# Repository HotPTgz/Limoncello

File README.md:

# Limoncello 🍋🎻

**Limoncello is a successor to the [LMN-3](https://github.com/FundamentalFrequency), the open-source DIY groovebox by Fundamental Frequency.** The LMN-3 is a lemon tree; Limoncello is what you make from the lemons, and it ends in *cello*.

It keeps the LMN-3's idea (a Raspberry Pi running a Tracktion-based DAW, a Teensy reading keys and encoders) and rebuilds the instrument around it:

| | Limoncello |
|---|---|
| Keys | 46 **Hall-effect** magnetic switches, **velocity-sensitive**, each with its own **RGB LED** |
| Screen | **7.9" 1280 × 400** bar screen (Waveshare), with DAW screens laid out for it |
| Audio | **Raspberry Pi Codec Zero** on board: two built-in **speakers**, a switched **headphone jack**, a **microphone** |
| Computer | **Raspberry Pi 5** with the official Active Cooler (the board is cut out around it) + **Teensy 4.1** |
| New controls | **MIC** key (record or sample from the mic), **joystick click** (sustain), Control + click (mod wheel on/off) |
| Case | 3D-printed, **flat top**: screen, speakers and keys flush; encoders in a sunken pocket; two lid options |
| Power | mains, or an optional **power bank cradle** (4.5–5 h) |

> **Project status: prototype.** The board, case, firmware and software are designed and checked in CAD and in simulation: design rule checks, interference checks between every part, unit tests, and the app running on a computer. A full Limoncello has **not been built yet**. A 4-key test board is being made to confirm the Hall-effect keys before the main board is ordered. See [What's still open](#whats-still-open).

## Where everything is

| Folder | What's in it |
|---|---|
| [`hardware/main-board/`](hardware/main-board) | The main PCB (rev C, 330 × 180 mm, 2 layers): KiCad project, Gerbers ready for JLCPCB/PCBWay, BOM, pick-and-place, 3D model, key map |
| [`hardware/test-board/`](hardware/test-board) | A 4-key test board and sketch, to try the Hall-effect keys before ordering the big board |
| [`enclosure/`](enclosure) | The printed case: OpenSCAD sources and ready-to-print STLs, the flush-key test piece, the power bank cradle, renders |
| [`firmware/`](firmware) | Teensy 4.1 firmware (PlatformIO): keys, velocity, LEDs, encoders, joystick |
| Software | The DAW lives in its own repository, because it is GPL: **[HotPTgz/lmn-3-daw, branch `lmn3-v3-wide`](https://github.com/HotPTgz/lmn-3-daw/tree/lmn3-v3-wide)** |
| [`docs/`](docs) | The [build guide](docs/BUILD.md), [shopping list](docs/SHOPPING_LIST.md), [software setup](docs/SOFTWARE.md), [controls](docs/CONTROLS.md), [power](docs/POWER.md) and [what has been verified](docs/VERIFICATION.md) |

## Build it

Start with **[docs/BUILD.md](docs/BUILD.md)**. It goes from ordering parts to the first sound, in this order:

1. Try the keys on the **test board** (optional, cheap, recommended).
2. Order the **parts** ([shopping list](docs/SHOPPING_LIST.md)) and the **main board**.
3. **Assemble** the board, flash the **Teensy**.
4. Set up the **Raspberry Pi** and build the **software** ([SOFTWARE.md](docs/SOFTWARE.md)).
5. **Print** and assemble the **case**.

Roughly: $520 of core parts, plus either $200 for factory assembly of the small surface-mount parts or $35 of parts to solder yourself. The battery option is about $90 more.

## A look inside

| | |
|---|---|
|  |  |
| The DAW's screens laid out for the 7.9" bar: the knob boxes sit in a 2 × 2 grid, like the encoders beside the screen | Control + MIC samples a sound straight onto a drum pad or into the sampler |
|  |  |
| The Pi 5 hangs under the board; the board is cut around its cooler, measured from Raspberry Pi's official 3D model | The optional power bank cradle also tilts the instrument 8° towards you |

## What's still open

- **The screen's HDMI cable route.** The Pi's micro-HDMI ports sit at the rear wall, while the screen's HDMI port is inside, so the cable either loops outside the case or goes through a micro-HDMI ribbon kit. Neither is built into the case yet. See [BUILD.md](docs/BUILD.md#the-screens-hdmi-cable).
- **The key gap** (`GAP` in the case) will be set from the flush-key test piece.
- **The joystick height** used for the lids is an estimate. Measure it when you have one.
- **Recording from the mic onto a track** and the app on the real 7.9" screen still need trying on real hardware.

Issues and pull requests are welcome, especially from people who build one.

## Credits and licences

Limoncello stands on the **LMN-3 by [Fundamental Frequency](https://github.com/FundamentalFrequency)**: [LMN-3-ECAD](https://github.com/FundamentalFrequency/LMN-3-ECAD), [LMN-3-DAW](https://github.com/FundamentalFrequency/LMN-3-DAW) and [LMN-3-Firmware](https://github.com/FundamentalFrequency/LMN-3-Firmware). The DAW is built on [Tracktion Engine](https://github.com/Tracktion/tracktion_engine) and [JUCE](https://juce.com).

| Part | Licence |
|---|---|
| Hardware (`hardware/`) and enclosure (`enclosure/`) | [CC BY-SA 4.0](LICENSES/CC-BY-SA-4.0.txt), like the LMN-3 hardware it derives from |
| Firmware (`firmware/`) | [GPL-3.0](firmware/LICENSE), like LMN-3-Firmware |
| Software ([lmn-3-daw fork](https://github.com/HotPTgz/lmn-3-daw)) | GPL-3.0, like LMN-3-DAW |
| `enclosure/source/pi5_official.stl` | Raspberry Pi Ltd's Pi 5 3D model, MIT ([licence](enclosure/source/pi5_official.LICENSE.txt)) |

Raspberry Pi is a trademark of Raspberry Pi Ltd. Waveshare, UGREEN, Gateron and the other product names belong to their owners; they are named only to say which parts fit.

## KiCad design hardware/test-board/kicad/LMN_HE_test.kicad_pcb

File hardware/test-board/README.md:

# Limoncello Hall-effect key test board

This is a 4-key test board that uses exactly the same key footprint as rev C:
- the MT9105ET Hall sensor under the switch;
- the SK6812MINI-E LED with its window and 100 nF capacitor;
- the same 74AHCT1G125 LED data buffer.

Use it to check that the sensor and Gateron magnetic switch combination works before you order the full 330 × 180 mm board.
The board is 87 × 42 mm, 2 layers. Design check (DRC): 0 errors, 0 unconnected.

## What's in here
| File | Use |
|---|---|
| `LMN_HE_test_gerbers.zip` | Upload to JLCPCB (2 layers, 1.6 mm, any colour). Five boards cost a few dollars. |
| `LMN_HE_test_BOM.csv`, `*_positions.csv` | Parts list and KiCad placement file. |
| `jlcpcb/` | Ready-to-upload files for having JLCPCB solder the SMD parts (BOM + CPL with LCSC numbers, Gerber zip). See its README. |
| `plate/test_plate.stl` (+ `.scad`) | 3D-printable switch plate: 1.5 mm plate on 3.5 mm legs, M2 screws. |
| `firmware/` | Test sketch for the Teensy 4.1 (PlatformIO or Arduino IDE). |
| `kicad/` | KiCad 7 project. |

## Parts to buy

If JLCPCB assembled your boards, skip the LCSC list: you only need the rest.

**From LCSC** (they sell passives in strips of 20–100, so you get spares for cents):

| Part | Refs | Qty to order | LCSC |
|---|---|---|---|
| MT9105ET Hall sensor, SOT-23 | SW1–SW4 | 10 (4 + spares) | C967861 |
| SK6812MINI-E reverse-mount LED | LED1–LED4 | 5 | C5149201 |
| 74AHCT1G125 buffer, SOT-23-5 | U1 | 5 (minimum order) | C12494 |
| 100 nF 0805 | C1–C5 | 1 strip | C49678 |
| 1 µF 0805 | C7 | 1 strip | C28323 |
| 330 Ω 0805 | R1 | 1 strip | C17630 |
| 10 µF 1206 (22 µF is fine too) | C6 | 1 strip | C12891 (22 µF) |

**Other parts:**
- **Teensy 4.1** with pins. Your existing LMN-3's Teensy works for the test.
- **4 × Gateron Magnetic Jade switches.** Use the same switch you plan to use for the full build.
- **1 × 1×8 pin header**, 2.54 mm, plus **8 female–female jumper wires** to the Teensy. If your Teensy has no headers, use female–male wires to a breadboard instead.
- **4 × M2 nuts**, plus either **4 × M2×10 screws** (plate only) or **4 × M2×35 screws** (plate + flush test panel). Get the M2×35 if you'll print the flush test, which you should.
- **Micro-USB cable** (data, not charge-only) from the Teensy to your computer.

## Parts to print

| File | Qty | Notes |
|---|---|---|
| `plate/test_plate.stl` | 1 | Switch plate: holds the 4 switches. PLA, 0.2 mm, flat side down. Same file as `enclosure/flush_test/test_switch_plate.stl`. |
| `enclosure/flush_test/flush_test_panel.stl` | 1 | Flush-key test panel: a piece of the case top with 4 openings at gaps of 0.35, 0.45, 0.55 and 0.65 mm. Print it top-down, like the real top shell. |
| `enclosure/flush_test/flush_test_tiles_all.stl` | 1 set | The 4 key tiles: 2 white, 1 raised black, 1 menu tile (REC). Print in the colours and settings you'll use for the real keys. |

Print the panel and tiles on the printer and filament you'll use for the case, because the gap you pick depends on both.

## Assembly
1. **Top side:** solder the 4 Hall sensors. Keep them flat and centred on their pads, because that sets the distance to the magnet.
2. **Bottom side:**
   - Solder the LEDs. They sit in the windows, facing up through the board. The small triangle on the silkscreen marks pin 1.
   - Solder the capacitors, U1 and R1.
3. Solder the 1×8 header on the top side.
4. Screw the printed plate on, clip the 4 switches into the plate, and push them down until they sit flat on the board. HE switches have no metal pins: the plate is what holds them.

## Wiring to the Teensy 4.1
| Test board J1 | Teensy |
|---|---|
| 3V3 | 3.3V |
| GND | GND |
| 5V | VIN (USB 5 V) |
| LED | pin 17 |
| K1, K2, K3, K4 | pins 14, 15, 16, 18 |

These are the same pins the rev C board uses.

## Running the test
1. Flash `firmware/` with PlatformIO (`pio run -t upload`). Or open `LMN_HE_test/LMN_HE_test.ino` in the Arduino IDE with Teensyduino and set **Tools > USB Type: Serial + MIDI**.
2. Plug in the USB cable and **keep your hands off the keys for 2 seconds** while it measures the resting values. The LEDs go blue, then green.
3. Open the Serial Plotter to see the four readings live. Each LED goes from blue to red as you press its key.
4. Press every key all the way down a few times, both slowly and fast.
5. Type `r` in the serial monitor to get the report. It says **PASS** or **CHECK** for each key.
6. Optional:
   - Type `v`, then play: it shows the time between the two thresholds and the velocity of every note.
   - Open any synth or DAW on your computer: the keys play C, D, E and F with velocity.

## What the numbers mean
| Result | Meaning | What to do |
|---|---|---|
| **swing ≥ 200 counts, noise ≤ 10 p-p, keys within ±30 %** | Good: the sensor sees enough change and velocity will work well. | Order rev C as it is. |
| swing between 100 and 200 | It works, but the velocity resolution is coarse. | Still usable. Try a stronger-magnet switch, or lower `VEL_SLOW_US` in the main firmware's `config.h`. |
| swing < 100 | The sensor is too insensitive for this magnet, or a sensor sits crooked. | Re-check the soldering. If all keys are low, the sensor choice needs to change before ordering rev C. |
| noisy (> 10 p-p) | Supply or wiring noise. | Use short wires and twist GND with the signals. rev C has better grounding; the firmware can also average. |
| one key very different | Bad solder joint, tilted sensor, or a switch not seated flat. | Reflow that sensor or reseat the switch, then press `c` and test again. |

Keep the report (`r`) and a screenshot of the plotter: they tell you how to set the thresholds in `firmware/src/config.h` for your switches. If your results are unusual, please share them in an issue.

## Note for the full build
These switches need a **plate** (1.5 mm) to hold them. The rev C plate is printed in two halves: `enclosure/stl/plate_left.stl` and `plate_right.stl`.

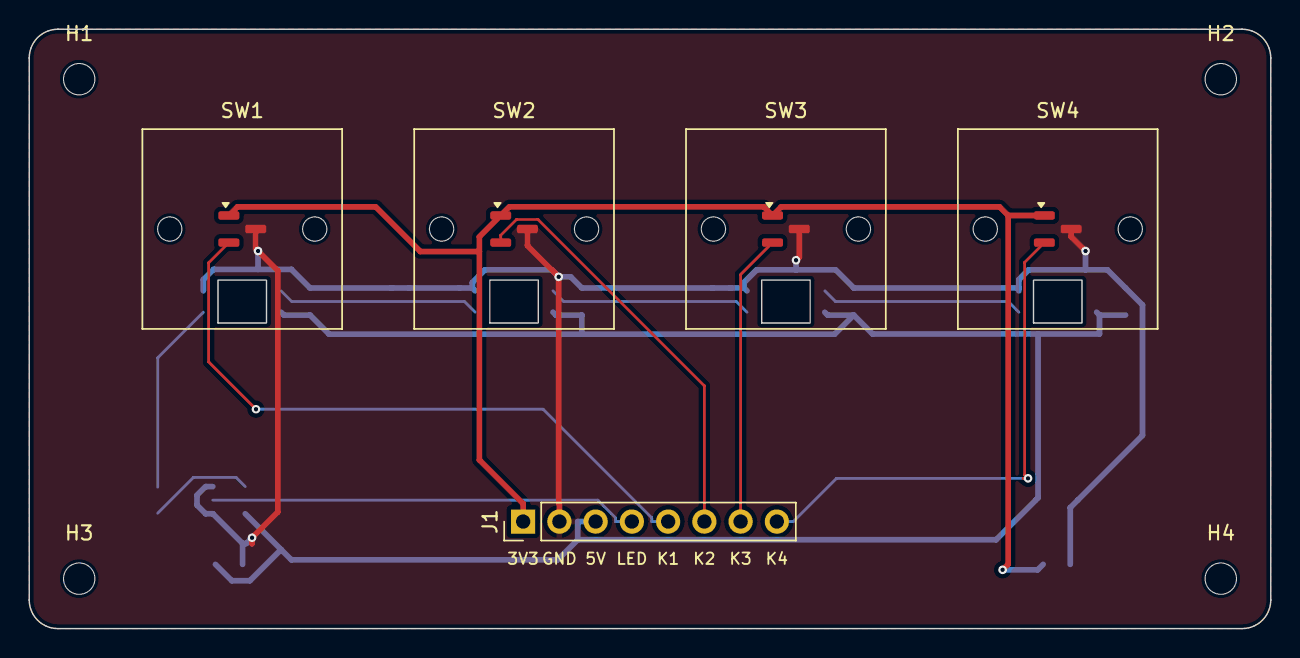
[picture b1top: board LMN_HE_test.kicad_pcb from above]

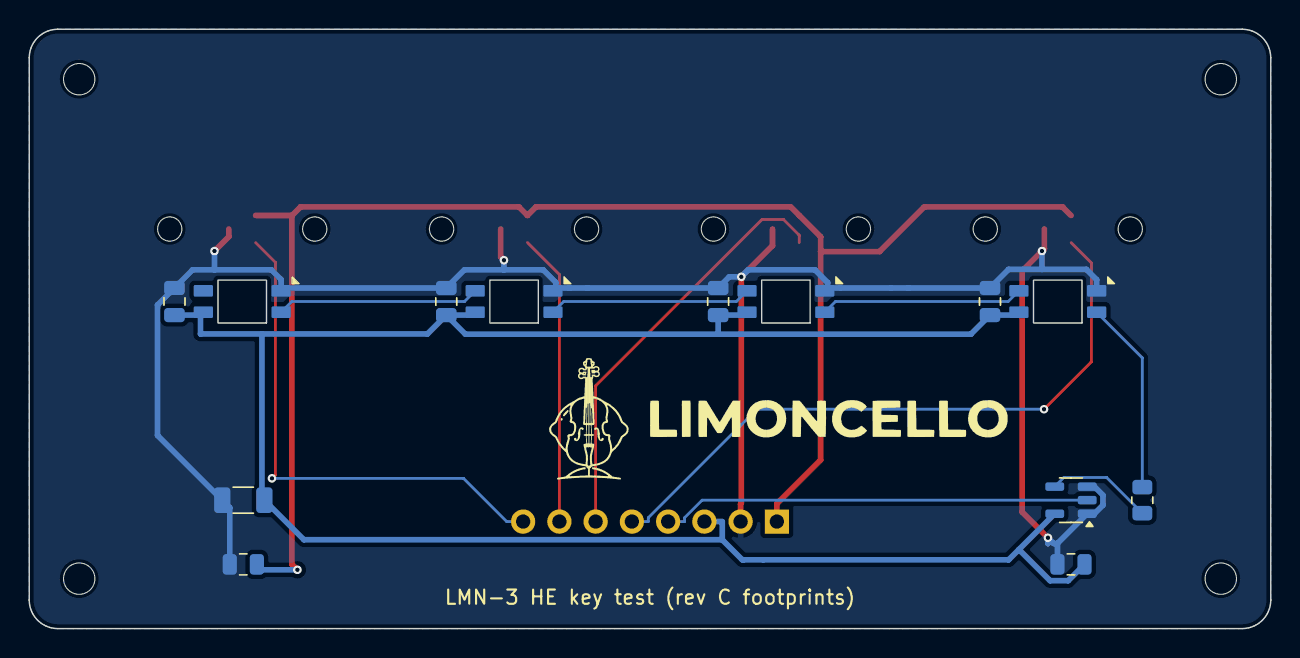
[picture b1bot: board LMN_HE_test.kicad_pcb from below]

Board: 2 copper layers, 87.0 x 42.0 mm, 23 parts (14 on the bottom side), 13 nets.

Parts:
C1, C2, C3, C4, C5: 100nF; C_0805_2012Metric
C6: 10uF; C_1206_3216Metric
C7: 1uF; C_0805_2012Metric
H1, H2, H3, H4: M2; MountingHole_2.2mm_M2
J1: To Teensy; PinHeader_1x08_P2.54mm_Vertical
LED1, LED2, LED3, LED4: SK6812MINI-E; SK6812MINI-E_MX_Reverse
LOGO1: Limoncello_badge_8mm
R1: 330R; R_0805_2012Metric
SW1, SW2, SW3, SW4: MT9105ET; SW_MX_HE_SOT23
U1: 74AHCT1G125; SOT-23-5

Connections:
+3V3: C7.1, J1.1, SW1.1, SW2.1, SW3.1, SW4.1
+5V: C1.1, C2.1, C3.1, C4.1, C5.1, C6.1, J1.3, LED1.1, LED2.1, LED3.1, LED4.1, U1.5
GND: C1.2, C2.2, C3.2, C4.2, C5.2, C6.2, C7.2, J1.2, LED1.3, LED2.3, LED3.3, LED4.3, SW1.3, SW2.3, SW3.3, SW4.3, U1.1, U1.3
LED_D0: LED1.4, R1.2
LED_D1: LED1.2, LED2.4
LED_D2: LED2.2, LED3.4
LED_D3: LED3.2, LED4.4
LED_DATA_3V3: J1.4, U1.2
LED_DATA_5V: R1.1, U1.4
OUT1: J1.5, SW1.2
OUT2: J1.6, SW2.2
OUT3: J1.7, SW3.2
OUT4: J1.8, SW4.2

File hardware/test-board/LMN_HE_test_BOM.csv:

Qty,Value,Footprint,Side,References
5,100nF,C_0805_2012Metric,bottom,C1 C2 C3 C4 C5
1,10uF,C_1206_3216Metric,bottom,C6
1,1uF,C_0805_2012Metric,bottom,C7
4,M2,MountingHole_2.2mm_M2,top,H1 H2 H3 H4
1,To Teensy,PinHeader_1x08_P2.54mm_Vertical,top,J1
4,SK6812MINI-E,SK6812MINI-E_MX_Reverse,bottom,LED1 LED2 LED3 LED4
1,330R,R_0805_2012Metric,bottom,R1
4,MT9105ET,SW_MX_HE_SOT23,top,SW1 SW2 SW3 SW4
1,74AHCT1G125,SOT-23-5,bottom,U1

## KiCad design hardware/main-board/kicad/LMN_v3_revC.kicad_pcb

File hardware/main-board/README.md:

# Limoncello main board (rev C): Hall-effect keys, RGB, 7.9" bar screen, Codec Zero audio

Board: 330 × 180 mm, 2 layers, 1.6 mm, GND pour on both layers.
DRC: 0 clearance errors, 0 unconnected. The only warnings left are silkscreen and library-path notices.

**Pi cooler opening (sized from the official Raspberry Pi drawings):** the rear edge is open over the Pi. Dimensions are measured from the board's left and rear edges.
- **Sources:** the Pi 5 STEP model and the Active Cooler mechanical drawing from Raspberry Pi.
- **Why it's needed:** the cooler stands about 10.5 mm above the Pi's top face. The gap between the Pi and this board (header plastic + socket) is 11 mm, so the cooler and its push pins need room above it.
- **Shape:** the opening runs x 107.5–197.3 mm, in three depth steps:
  - x 107.5–130.5: 56.5 mm deep, for the USB/Ethernet stack, which overhangs the Pi by 3 mm.
  - x 130.5–190.5: 50.3 mm deep, over the cooler body and fins.
  - x 190.5–197.3: 14.5 mm deep. The cooler corner here is empty, which leaves a routing corridor next to the GPIO header.
- **USB:** only the **lower** two USB ports and Ethernet are reachable. The board edge covers the upper USB pair.
- **Cables:** the opening also passes the HDMI and USB-C cables.
- **Mounting:** the cooler uses the Pi's two dedicated heatsink holes. The Pi is held by the GPIO header, **one M2.5 stand-off (H12)**, and three posts in the bottom tray under its other mounting holes. H11 was removed to make room for routing.
- **Routing:** the Pi → Codec Zero connections were re-routed around the opening.
  - Pin 17 (the second 3.3 V pin) is left unconnected on both J2 and J3. The Pi and the Codec Zero each tie it to pin 1 on their own board, so J2.1 → J3.1 feeds 3.3 V.
  - GPIO23/24/27 (the Codec Zero's LEDs and button) are no longer wired: they would be hidden inside the case anyway.

## What's on the board
- 46 Hall-effect keys (MT9105ET, per switch), 46 SK6812MINI-E LEDs, 6 × 74HC4051 → Teensy 4.1 (same as rev B, new layout).
- J2: underside socket for the Raspberry Pi 5 (held by the header, 1 M2.5 stand-off (H12) and 3 tray posts).
- **Audio**:
  - **J3:** a 2×20 male header wired in parallel with J2. The **Raspberry Pi Codec Zero** plugs onto it from below.
    - Its 40-pin female header goes onto J3, with its component side facing the case floor.
    - Its outline is drawn on Cmts.User/B.Fab.
  - **U9:** a PAM8403 stereo class-D amp, fed from the Codec Zero's Headphone/AUX OUT. It drives the two side speakers.
  - **J5:** a switched 3.5 mm headphone jack (CUI SJ1-3535NG) on the right edge. Plugging in headphones disconnects the amp input, so the speakers go silent. No software is involved.
  - **MK1:** a 6 mm electret capsule under the mic pinhole in front of the screen. J8 runs it to the Codec Zero's external-mic 3.5 mm socket.
    - Plugging into that socket disables the Codec Zero's built-in MEMS mic automatically.
  - **Q1 (2N7002):** lets GPIO22 mute the speakers. GPIO22 low or floating = amp on (default); GPIO22 high = mute.
  - **Other pins wired through to J3:** ID_SD/ID_SC (HAT EEPROM auto-config).

## Cables you make
| From | To | Notes |
|---|---|---|
| Codec Zero **P2 (AUX OUT)** pads | **J4** (JST-PH 3-pin: 1 = L, 2 = GND, 3 = R) | Solder 3 wires to P2. **Check L/GND/R on the Codec Zero silkscreen** (pin 1 is the square pad). |
| **J8** (JST-PH 2-pin: 1 = mic +, 2 = GND) | Codec Zero mic socket | Mono 3.5 mm plug: tip = mic +, sleeve = GND. Shielded cable. |
| **J6 / J7** (JST-PH 2-pin) | Left / right speaker | 40 mm, 4–8 Ω, 2–3 W. Run the leads down through the speaker's 42 mm hole in the board. J6 and J7 are both on the right, so the **left lead needs about 30 cm**, the right about 12 cm. Twist each pair. Never connect either output terminal to GND (bridged outputs). |

## Software (Raspberry Pi OS)
1. With J3 wired to the HAT EEPROM, the Codec Zero is usually detected automatically. If it isn't, add `dtoverlay=rpi-codeczero` to `/boot/firmware/config.txt` (older images use `dtoverlay=iqaudio-codec`). Also comment out `dtparam=audio=on`.
2. Load a mixer preset from Raspberry Pi's **Pi-Codec** repository (github.com/raspberrypi/Pi-Codec). Use the external-mic record + AUX OUT playback state, then `sudo alsactl store`.
3. The speaker level is set by the codec's **Headphone** volume, because the amp gain is fixed by R2/R3 (82 kΩ ≈ +9 dB). Start low.
4. In LMN-3-DAW (Tracktion), select the "Zero" card as both the input and the output device.

## Power notes
Everything is fed from the Pi's 5 V rail (pins 2/4), so use the official 27 W (5 V 5 A) USB-C supply.
- The 46 LEDs can draw up to about 2.7 A at full white.
- Cap brightness in the Teensy firmware (about 25% is plenty).
- The amp draws up to about 1 A on loud peaks.

## Files
- `gerbers/` + `*_gerbers.zip`: upload the zip to JLCPCB/PCBWay.
- `jlcpcb/`: BOM and placement (CPL) files in JLCPCB format, with LCSC part numbers, for having the SMD parts assembled. See its README.
- `*_BOM.csv`, `*_positions.csv`: BOM and pick-and-place (most SMD parts are on the bottom side).
- `*.step`: 3D model of the board.
- `kicad/`: KiCad 7 project with the custom footprints.
- `LMN_v3_mux_map.csv`, `LMN_v3_keys.json`: key ↔ mux channel ↔ Teensy pin map (needed for the firmware).

## Before you order
- Print the board 1:1 on paper. Check the Codec Zero, Pi 5 and screen positions against the real parts.
- Check that the Codec Zero (on J3, plus its female header) clears the case floor. It needs about 20 mm below the PCB.

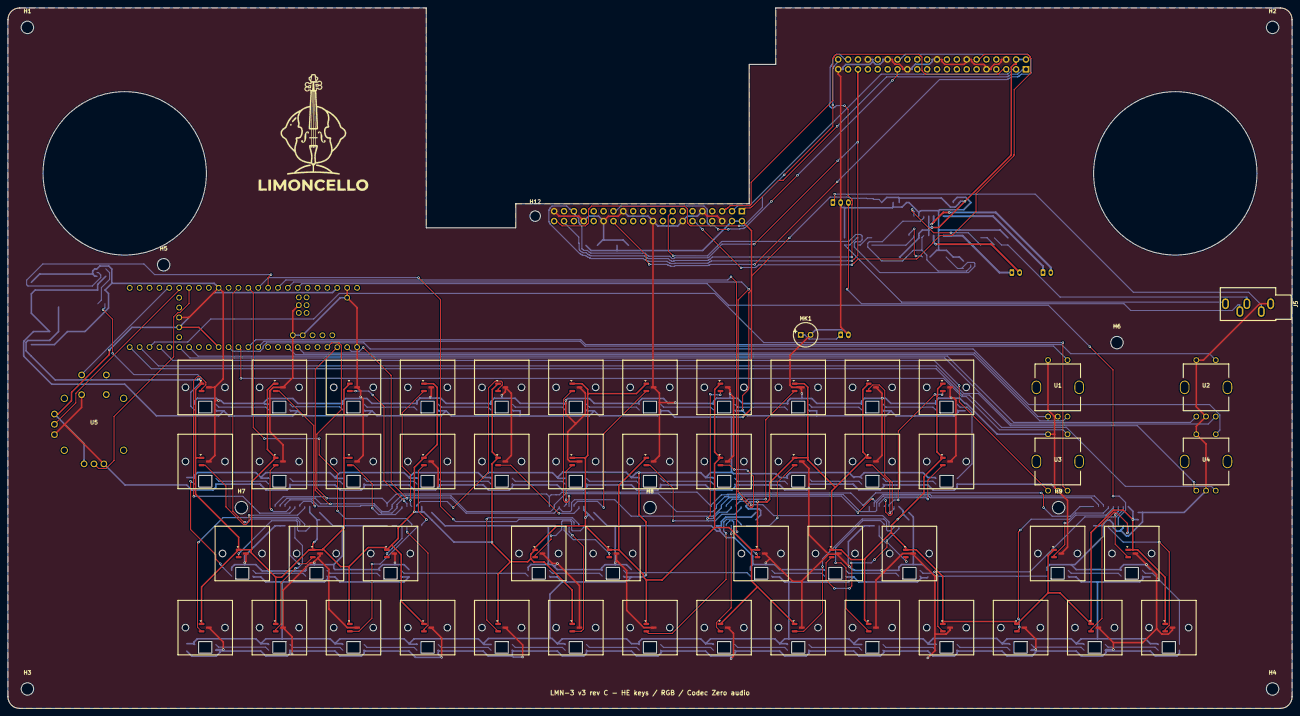
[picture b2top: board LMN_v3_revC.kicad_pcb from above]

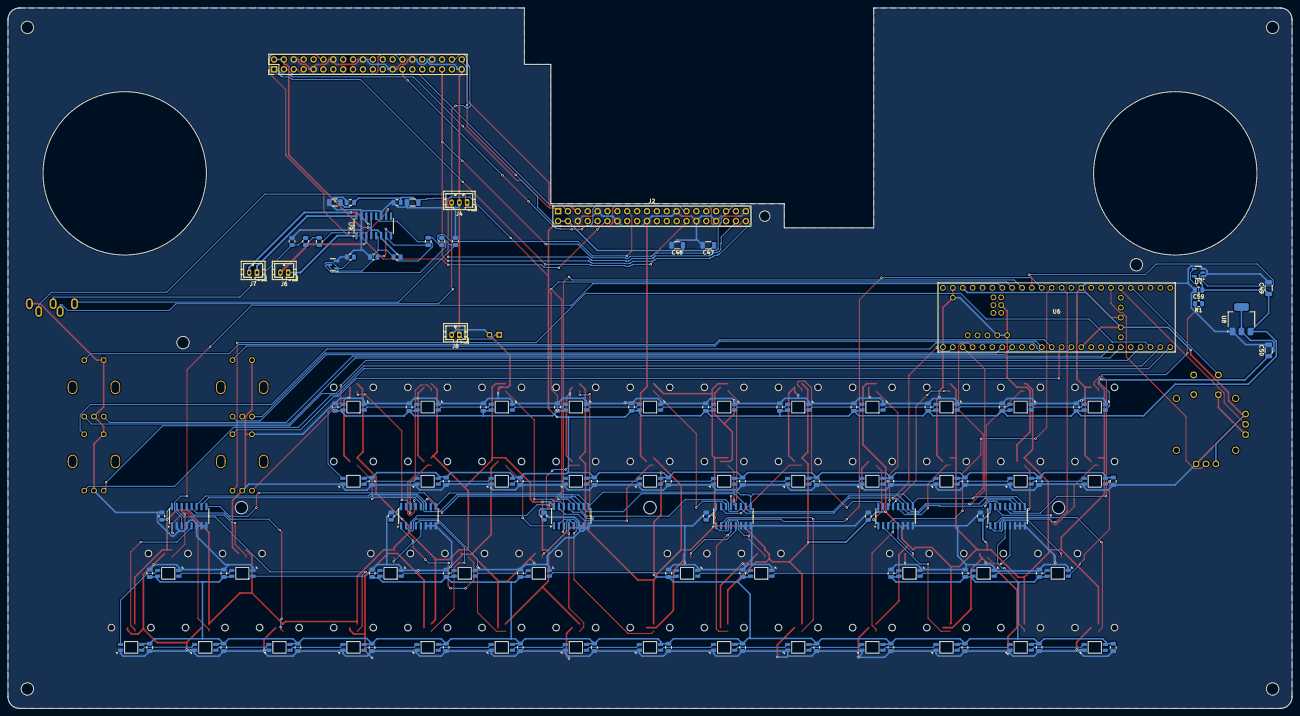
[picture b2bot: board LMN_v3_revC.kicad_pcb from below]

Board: 2 copper layers, 330.0 x 180.0 mm, 198 parts (133 on the bottom side), 147 nets.

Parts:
C1, C2, C3, C4, C5, C6, C7, C8, C9, C10, C11, C12, C13, C14, C15, C16, C17, C18, C19, C20, C21, C22, C23, C24, C25, C26, C27, C28, C29, C30, C31, C32, C33, C34, C35, C36, C37, C38, C39, C40, C41, C42, C43, C44, C45, C46, C59, C60, C61, C62, C63, C64, C65: 100nF; C_0805_2012Metric
C47, C48, C49, C50, C54, C55: 22uF 10V; C_1206_3216Metric
C51, C52: 0.47uF; C_0805_2012Metric
C53, C56, C57: 1uF; C_0805_2012Metric
H1, H2, H3, H4, H5, H6, H7, H8, H9: M3; MountingHole_3.2mm_M3
H12: Pi M2.5; MountingHole_2.7mm_M2.5
J2: RPi 5 GPIO socket; RPi_GPIO_Socket_2x20_Underside
J3: Codec Zero header; PinHeader_2x20_P2.54mm_Vertical
J4: AUX OUT from Codec Zero P2; JST_PH_B3B-PH-K_1x03_P2.00mm_Vertical
J5: SJ1-3535NG; Jack_3.5mm_CUI_SJ1-3535NG_Horizontal
J6: Speaker L; JST_PH_B2B-PH-K_1x02_P2.00mm_Vertical
J7: Speaker R; JST_PH_B2B-PH-K_1x02_P2.00mm_Vertical
J8: Mic to Codec Zero (3.5 mm plug); JST_PH_B2B-PH-K_1x02_P2.00mm_Vertical
LED1, LED2, LED3, LED4, LED5, LED6, LED7, LED8, LED9, LED10, LED11, LED12, LED13, LED14, LED15, LED16, LED17, LED18, LED19, LED20, LED21, LED22, LED23, LED24, LED25, LED26, LED27, LED28, LED29, LED30, LED31, LED32, LED33, LED34, LED35, LED36, LED37, LED38, LED39, LED40, LED41, LED42, LED43, LED44, LED45, LED46: SK6812MINI-E; SK6812MINI-E_MX_Reverse
LOGO1: Limoncello_logo_30mm
MK1: Electret 6mm; MIC_Electret_6mm_THT
Q1: 2N7002; SOT-23
R1: 330R; R_0805_2012Metric
R2, R3: 82k; R_0805_2012Metric
R4, R5, R7: 100k; R_0805_2012Metric
R6: 10k; R_0805_2012Metric
SW1, SW2, SW3, SW4, SW5, SW6, SW7, SW8, SW9, SW10, SW11, SW12, SW13, SW14, SW15, SW16, SW17, SW18, SW19, SW20, SW21, SW22, SW23, SW24, SW25, SW26, SW27, SW28, SW29, SW30, SW31, SW32, SW33, SW34, SW35, SW36, SW37, SW38, SW39, SW40, SW41, SW42, SW43, SW44, SW45, SW46: MT9105ET; SW_MX_HE_SOT23
U1, U2, U3, U4: EC11E; EC11E_H20
U5: COM-09032
U6: Teensy 4.1; teensy_4.1
U7: 74AHCT1G125; SOT-23-5
U8: AMS1117-3.3; SOT-223-3_TabPin2
U9: PAM8403DR; SOP-16_3.9x9.9mm_P1.27mm
U10, U11, U12, U13, U14, U15: 74HC4051; SOIC-16_3.9x9.9mm_P1.27mm

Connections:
5: U1.A, U6.5
6: U1.B, U6.6
26: U2.A, U6.26
27: U2.B, U6.27
29: U3.A, U6.29
30: U3.B, U6.30
31: U4.A, U6.31
32: U4.B, U6.32
38: U5.V2, U6.38
39: U5.H2, U6.39
+3V3: U5.H1, U5.V1, U6.3.3V
+3V3_HE: C50.1, C60.1, C61.1, C62.1, C63.1, C64.1, C65.1, SW1.1, SW2.1, SW3.1, SW4.1, SW5.1, SW6.1, SW7.1, SW8.1, SW9.1, SW10.1, SW11.1, SW12.1, SW13.1, SW14.1, SW15.1, SW16.1, SW17.1, SW18.1, SW19.1, SW20.1, SW21.1, SW22.1, SW23.1, SW24.1, SW25.1, SW26.1, SW27.1, SW28.1, SW29.1, SW30.1, SW31.1, SW32.1, SW33.1, SW34.1, SW35.1, SW36.1, SW37.1, SW38.1, SW39.1, SW40.1, SW41.1, SW42.1, SW43.1, SW44.1, SW45.1, SW46.1, U8.2, U10.16, U11.16, U12.16, U13.16, U14.16, U15.16
+5V: C1.1, C2.1, C3.1, C4.1, C5.1, C6.1, C7.1, C8.1, C9.1, C10.1, C11.1, C12.2, C13.2, C14.2, C15.2, C16.2, C17.2, C18.2, C19.2, C20.2, C21.2, C22.2, C23.1, C24.1, C25.1, C26.1, C27.1, C28.1, C29.1, C30.1, C31.1, C32.1, C33.2, C34.2, C35.2, C36.2, C37.2, C38.2, C39.2, C40.2, C41.2, C42.2, C43.2, C44.2, C45.2, C46.2, C47.1, C48.1, C49.1, C54.1, C55.1, C56.1, C57.1, C59.1, J2.2, J2.4, J3.2, J3.4, LED1.1, LED2.1, LED3.1, LED4.1, LED5.1, LED6.1, LED7.1, LED8.1, LED9.1, LED10.1, LED11.1, LED12.1, LED13.1, LED14.1, LED15.1, LED16.1, LED17.1, LED18.1, LED19.1, LED20.1, LED21.1, LED22.1, LED23.1, LED24.1, LED25.1, LED26.1, LED27.1, LED28.1, LED29.1, LED30.1, LED31.1, LED32.1, LED33.1, LED34.1, LED35.1, LED36.1, LED37.1, LED38.1, LED39.1, LED40.1, LED41.1, LED42.1, LED43.1, LED44.1, LED45.1, LED46.1, R6.1, U7.5, U8.3, U9.4, U9.6, U9.13
AMP_EN: Q1.3, R6.2, U9.5, U9.12
AMP_INL: C51.1, U9.7
AMP_INR: C52.1, U9.10
AMP_L_R: C51.2, R2.1
AMP_L_RAW: J5.TN, R2.2, R4.1
AMP_MUTE: J2.15, Q1.1, R7.1
AMP_R_R: C52.2, R3.1
AMP_R_RAW: J5.RN, R3.2, R5.1
AMP_VREF: C53.1, U9.8
ENC1_SW: U1.E, U6.9
ENC2_SW: U2.E, U6.10
ENC3_SW: U3.E, U6.11
ENC4_SW: U4.E, U6.12
GND: C1.2, C2.2, C3.2, C4.2, C5.2, C6.2, C7.2, C8.2, C9.2, C10.2, C11.2, C12.1, C13.1, C14.1, C15.1, C16.1, C17.1, C18.1, C19.1, C20.1, C21.1, C22.1, C23.2, C24.2, C25.2, C26.2, C27.2, C28.2, C29.2, C30.2, C31.2, C32.2, C33.1, C34.1, C35.1, C36.1, C37.1, C38.1, C39.1, C40.1, C41.1, C42.1, C43.1, C44.1, C45.1, C46.1, C47.2, C48.2, C49.2, C50.2, C53.2, C54.2, C55.2, C56.2, C57.2, C59.2, C60.2, C61.2, C62.2, C63.2, C64.2, C65.2, J2.6, J2.9, J2.14, J2.20, J2.25, J2.30, J2.34, J2.39, J3.6, J3.9, J3.14, J3.20, J3.25, J3.30, J3.34, J3.39, J4.2, J5.S, J8.2, LED1.3, LED2.3, LED3.3, LED4.3, LED5.3, LED6.3, LED7.3, LED8.3, LED9.3, LED10.3, LED11.3, LED12.3, LED13.3, LED14.3, LED15.3, LED16.3, LED17.3, LED18.3, LED19.3, LED20.3, LED21.3, LED22.3, LED23.3, LED24.3, LED25.3, LED26.3, LED27.3, LED28.3, LED29.3, LED30.3, LED31.3, LED32.3, LED33.3, LED34.3, LED35.3, LED36.3, LED37.3, LED38.3, LED39.3, LED40.3, LED41.3, LED42.3, LED43.3, LED44.3, LED45.3, LED46.3, MK1.2, Q1.2, R4.2, R5.2, R7.2, SW1.3, SW2.3, SW3.3, SW4.3, SW5.3, SW6.3, SW7.3, SW8.3, SW9.3, SW10.3, SW11.3, SW12.3, SW13.3, SW14.3, SW15.3, SW16.3, SW17.3, SW18.3, SW19.3, SW20.3, SW21.3, SW22.3, SW23.3, SW24.3, SW25.3, SW26.3, SW27.3, SW28.3, SW29.3, SW30.3, SW31.3, SW32.3, SW33.3, SW34.3, SW35.3, SW36.3, SW37.3, SW38.3, SW39.3, SW40.3, SW41.3, SW42.3, SW43.3, SW44.3, SW45.3, SW46.3, U1.C, U1.D, U2.C, U2.D, U3.C, U3.D, U4.C, U4.D, U5.B2A, U5.H3, U5.V3, U6.GND, U7.1, U7.3, U8.1, U9.2, U9.11, U9.15, U10.6, U10.7, U10.8, U11.6, U11.7, U11.8, U12.6, U12.7, U12.8, U13.6, U13.7, U13.8, U14.6, U14.7, U14.8, U15.2, U15.4, U15.6, U15.7, U15.8
HE_SW1: SW1.2, U10.13
HE_SW2: SW2.2, U10.14
HE_SW3: SW3.2, U11.13
HE_SW4: SW4.2, U11.14
HE_SW5: SW5.2, U11.15
HE_SW6: SW6.2, U12.13
HE_SW7: SW7.2, U12.14
HE_SW8: SW8.2, U13.13
HE_SW9: SW9.2, U13.14
HE_SW10: SW10.2, U14.13
HE_SW11: SW11.2, U14.14
HE_SW12: SW12.2, U10.15
HE_SW13: SW13.2, U10.12
HE_SW14: SW14.2, U11.12
HE_SW15: SW15.2, U11.1
HE_SW16: SW16.2, U12.15
HE_SW17: SW17.2, U12.12
HE_SW18: SW18.2, U13.15
HE_SW19: SW19.2, U13.12
HE_SW20: SW20.2, U13.1
HE_SW21: SW21.2, U14.15
HE_SW22: SW22.2, U14.12
HE_SW23: SW23.2, U10.1
HE_SW24: SW24.2, U10.5
HE_SW25: SW25.2, U11.5
HE_SW26: SW26.2, U12.1
HE_SW27: SW27.2, U12.5
HE_SW28: SW28.2, U13.5
HE_SW29: SW29.2, U14.1
HE_SW30: SW30.2, U14.5
HE_SW31: SW31.2, U15.13
HE_SW32: SW32.2, U15.14
HE_SW33: SW33.2, U10.2
HE_SW34: SW34.2, U10.4
HE_SW35: SW35.2, U11.2
HE_SW36: SW36.2, U11.4
HE_SW37: SW37.2, U12.2
HE_SW38: SW38.2, U12.4
HE_SW39: SW39.2, U13.2
HE_SW40: SW40.2, U13.4
HE_SW41: SW41.2, U14.2
HE_SW42: SW42.2, U14.4
HE_SW43: SW43.2, U15.15
HE_SW44: SW44.2, U15.12
HE_SW45: SW45.2, U15.1
HE_SW46: SW46.2, U15.5
HP_L: J4.1, J5.T
HP_R: J4.3, J5.R
I2S_BCLK: J2.12, J3.12
I2S_DIN: J2.38, J3.38
I2S_DOUT: J2.40, J3.40
I2S_LRCLK: J2.35, J3.35
ID_SC: J2.28, J3.28
ID_SD: J2.27, J3.27
LED_D0: LED1.4, R1.2
LED_D1: LED1.2, LED2.4
LED_D2: LED2.2, LED3.4
LED_D3: LED3.2, LED4.4
LED_D4: LED4.2, LED5.4
LED_D5: LED5.2, LED6.4
LED_D6: LED6.2, LED7.4
LED_D7: LED7.2, LED8.4
LED_D8: LED8.2, LED9.4
LED_D9: LED9.2, LED10.4
LED_D10: LED10.2, LED11.4
LED_D11: LED11.2, LED12.4
LED_D12: LED12.2, LED13.4
LED_D13: LED13.2, LED14.4
LED_D14: LED14.2, LED15.4
LED_D15: LED15.2, LED16.4
LED_D16: LED16.2, LED17.4
LED_D17: LED17.2, LED18.4
LED_D18: LED18.2, LED19.4
LED_D19: LED19.2, LED20.4
LED_D20: LED20.2, LED21.4
LED_D21: LED21.2, LED22.4
LED_D22: LED22.2, LED23.4
LED_D23: LED23.2, LED24.4
LED_D24: LED24.2, LED25.4
LED_D25: LED25.2, LED26.4
LED_D26: LED26.2, LED27.4
LED_D27: LED27.2, LED28.4
LED_D28: LED28.2, LED29.4
LED_D29: LED29.2, LED30.4
LED_D30: LED30.2, LED31.4
LED_D31: LED31.2, LED32.4
LED_D32: LED32.2, LED33.4
LED_D33: LED33.2, LED34.4
LED_D34: LED34.2, LED35.4
LED_D35: LED35.2, LED36.4
LED_D36: LED36.2, LED37.4
LED_D37: LED37.2, LED38.4
LED_D38: LED38.2, LED39.4
LED_D39: LED39.2, LED40.4
LED_D40: LED40.2, LED41.4
LED_D41: LED41.2, LED42.4
LED_D42: LED42.2, LED43.4
LED_D43: LED43.2, LED44.4
LED_D44: LED44.2, LED45.4
LED_D45: LED45.2, LED46.4
LED_DATA_3V3: U6.17, U7.2
LED_DATA_5V: R1.1, U7.4
MIC_IN: J8.1, MK1.1
MUX1_COM: U6.14, U10.3
MUX2_COM: U6.15, U11.3
MUX3_COM: U6.16, U12.3
MUX4_COM: U6.18, U13.3
MUX5_COM: U6.19, U14.3
MUX6_COM: U6.20, U15.3
MUX_S0: U6.0, U10.11, U11.11, U12.11, U13.11, U14.11, U15.11
MUX_S1: U6.1, U10.10, U11.10, U12.10, U13.10, U14.10, U15.10
MUX_S2: U6.2, U10.9, U11.9, U12.9, U13.9, U14.9, U15.9
PI_3V3: J2.1, J3.1
PI_SCL: J2.5, J3.5
PI_SDA: J2.3, J3.3
SEL: U5.B1A, U6.37
SPK_L+: J6.1, U9.1
SPK_L-: J6.2, U9.3
SPK_R+: J7.1, U9.16
SPK_R-: J7.2, U9.14

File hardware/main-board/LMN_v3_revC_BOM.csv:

Qty,Value,Footprint,Side,References
53,100nF,C_0805_2012Metric,bottom,C1 C2 C3 C4 C5 C6 C7 C8 C9 C10 C11 C12 C13 C14 C15 C16 C17 C18 C19 C20 C21 C22 C23 C24 C25 C26 C27 C28 C29 C30 C31 C32 C33 C34 C35 C36 C37 C38 C39 C40 C41 C42 C43 C44 C45 C46 C59 C60 C61 C62 C63 C64 C65
6,22uF 10V,C_1206_3216Metric,bottom,C47 C48 C49 C50 C54 C55
2,0.47uF,C_0805_2012Metric,bottom,C51 C52
3,1uF,C_0805_2012Metric,bottom,C53 C56 C57
9,M3,MountingHole_3.2mm_M3,top,H1 H2 H3 H4 H5 H6 H7 H8 H9
1,Pi M2.5,MountingHole_2.7mm_M2.5,top,H12
1,RPi 5 GPIO socket,RPi_GPIO_Socket_2x20_Underside,top,J2
1,Codec Zero header,PinHeader_2x20_P2.54mm_Vertical,bottom,J3
1,AUX OUT from Codec Zero P2,JST_PH_B3B-PH-K_1x03_P2.00mm_Vertical,bottom,J4
1,SJ1-3535NG,Jack_3.5mm_CUI_SJ1-3535NG_Horizontal,top,J5
1,Speaker L,JST_PH_B2B-PH-K_1x02_P2.00mm_Vertical,bottom,J6
1,Speaker R,JST_PH_B2B-PH-K_1x02_P2.00mm_Vertical,bottom,J7
1,Mic to Codec Zero (3.5 mm plug),JST_PH_B2B-PH-K_1x02_P2.00mm_Vertical,bottom,J8
46,SK6812MINI-E,SK6812MINI-E_MX_Reverse,bottom,LED1 LED2 LED3 LED4 LED5 LED6 LED7 LED8 LED9 LED10 LED11 LED12 LED13 LED14 LED15 LED16 LED17 LED18 LED19 LED20 LED21 LED22 LED23 LED24 LED25 LED26 LED27 LED28 LED29 LED30 LED31 LED32 LED33 LED34 LED35 LED36 LED37 LED38 LED39 LED40 LED41 LED42 LED43 LED44 LED45 LED46
1,Electret 6mm,MIC_Electret_6mm_THT,top,MK1
1,2N7002,SOT-23,bottom,Q1
1,330R,R_0805_2012Metric,bottom,R1
2,82k,R_0805_2012Metric,bottom,R2 R3
3,100k,R_0805_2012Metric,bottom,R4 R5 R7
1,10k,R_0805_2012Metric,bottom,R6
46,MT9105ET,SW_MX_HE_SOT23,top,SW1 SW2 SW3 SW4 SW5 SW6 SW7 SW8 SW9 SW10 SW11 SW12 SW13 SW14 SW15 SW16 SW17 SW18 SW19 SW20 SW21 SW22 SW23 SW24 SW25 SW26 SW27 SW28 SW29 SW30 SW31 SW32 SW33 SW34 SW35 SW36 SW37 SW38 SW39 SW40 SW41 SW42 SW43 SW44 SW45 SW46
4,EC11E,EC11E_H20,top,U1 U2 U3 U4
6,74HC4051,SOIC-16_3.9x9.9mm_P1.27mm,bottom,U10 U11 U12 U13 U14 U15
1,COM-09032,COM-09032,top,U5
1,Teensy 4.1,teensy_4.1,bottom,U6
1,74AHCT1G125,SOT-23-5,bottom,U7
1,AMS1117-3.3,SOT-223-3_TabPin2,bottom,U8
1,PAM8403DR,SOP-16_3.9x9.9mm_P1.27mm,bottom,U9

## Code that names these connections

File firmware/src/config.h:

// LMN-3 v3 (rev C) firmware configuration.
// Based on the original LMN-3 firmware (FundamentalFrequency/LMN-3-Firmware, GPL-3.0).
#pragma once
#include <Arduino.h>

// ---------------------------------------------------------------- MIDI
// CC numbers are identical to the original firmware so LMN-3-DAW works unchanged.
const uint8_t MIDI_CH = 1;
const uint8_t ENCODER_1 = 3, ENCODER_2 = 9, ENCODER_3 = 14, ENCODER_4 = 15;
const uint8_t ENCODER_1_BUTTON = 20, ENCODER_2_BUTTON = 21, ENCODER_3_BUTTON = 22, ENCODER_4_BUTTON = 23;
const uint8_t UNDO_BUTTON = 24, TEMPO_BUTTON = 25, SAVE_BUTTON = 26;
const uint8_t SETTINGS_BUTTON = 85, TRACKS_BUTTON = 86, MIXER_BUTTON = 88, PLUGINS_BUTTON = 89;
const uint8_t MODIFIERS_BUTTON = 90, SEQUENCERS_BUTTON = 102;
const uint8_t LOOP_IN_BUTTON = 103, LOOP_OUT_BUTTON = 104, LOOP_BUTTON = 105;
const uint8_t CUT_BUTTON = 106, PASTE_BUTTON = 107, SLICE_BUTTON = 108;
const uint8_t RECORD_BUTTON = 109, PLAY_BUTTON = 110, STOP_BUTTON = 111, CONTROL_BUTTON = 112;
const uint8_t OCTAVE_CHANGE = 117, PLUS_BUTTON = 118, MINUS_BUTTON = 119;
// New on rev C (need a mapping in LMN-3-DAW to do something):
const uint8_t MIC_BUTTON = 113;        // the new "mic" key
const uint8_t JOYSTICK_BUTTON = 114;   // joystick click
const uint8_t MOD_WHEEL = 1;           // joystick Y axis (if switched on)
const uint8_t MOD_WHEEL_STATE = 115;   // sent when Control + joystick click switches the mod wheel (127 on, 0 off)
const uint8_t VELOCITY_STATE = 116;    // sent when Control + Tempo switches key velocity (127 on, 0 off = fixed velocity)

// ---------------------------------------------------------------- pins (rev C PCB)
const uint8_t PIN_MUX_S0 = 0, PIN_MUX_S1 = 1, PIN_MUX_S2 = 2;
const uint8_t PIN_MUX_COM[6] = {14, 15, 16, 18, 19, 20};   // A0 A1 A2 A4 A5 A6
const uint8_t PIN_LED_DATA = 17;                           // -> 74AHCT1G125 -> LED chain
const uint8_t PIN_ENC[4][2] = {{5, 6}, {26, 27}, {29, 30}, {31, 32}};
const uint8_t PIN_ENC_SW[4] = {9, 10, 11, 12};
const uint8_t PIN_JOY_X = 39, PIN_JOY_Y = 38, PIN_JOY_SEL = 37;

// ---------------------------------------------------------------- Hall-effect keys
// Key travel is normalised to 0..1000 (per-mille of the calibrated span).
const uint16_t DEFAULT_SPAN   = 300;   // ADC counts (12 bit) rest->bottom before calibration; grows automatically
const uint16_t MIN_SPAN       = 80;
const uint8_t  MUX_SETTLE_US  = 3;
// menu keys
const int16_t MENU_PRESS      = 500;   // actuation point
const int16_t MENU_RELEASE    = 300;
// piano keys: velocity = time between crossing VEL_LOW and VEL_HIGH
const int16_t VEL_LOW         = 150;
const int16_t VEL_HIGH        = 700;   // note-on point
const int16_t NOTE_OFF_POINT  = 100;
const uint32_t VEL_FAST_US    = 3000;  // <= this -> velocity 127
const uint32_t VEL_SLOW_US    = 60000; // >= this -> velocity 1
const float    VEL_CURVE      = 1.4f;  // >1 = need to play harder for loud notes
const bool     ENABLE_VELOCITY = true;  // the default; Control + Tempo switches it (remembered)
const uint8_t  FIXED_VELOCITY  = 100;   // what every note gets while velocity is off
const bool     ENABLE_POLY_AFTERTOUCH = false;   // pressure from the last part of the travel
const int16_t  AFTERTOUCH_START = 850;

// ---------------------------------------------------------------- joystick
const bool    JOY_X_INVERT = true;     // original firmware: right = higher pitch with this board orientation
const int16_t JOY_DEADZONE = 40;       // ADC counts around centre
const bool    ENABLE_MOD_WHEEL = false; // the default; Control + joystick click switches it (remembered)
const bool    ENABLE_JOYSTICK_BUTTON = true;

// ---------------------------------------------------------------- octave
const int8_t MAX_TRANSPOSITION = 4;    // +-4 octaves, as the original

// ---------------------------------------------------------------- LEDs (SK6812MINI-E, GRB)
// 46 LEDs at full white can draw ~2.7 A from the Pi's 5 V rail; keep this low.
const uint8_t LED_MAX_BRIGHTNESS = 64; // 0..255 hard cap (~25 %)
const uint8_t LED_IDLE_LEVEL     = 40; // 0..255, base glow relative to full
const uint16_t LED_FADE_MS       = 350;
const uint8_t HOST_LED_CHANNEL   = 16; // Pi -> Teensy LED control (see README)

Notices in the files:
parts and their libraries:
Geometry after marbastlib SW_MX_HE_0deg_1u (CERN-OHL-P).
Pad geometry and pairing after marbastlib LED_MX_6028R / MX_SK6812MINI-E (CERN-OHL-P).
